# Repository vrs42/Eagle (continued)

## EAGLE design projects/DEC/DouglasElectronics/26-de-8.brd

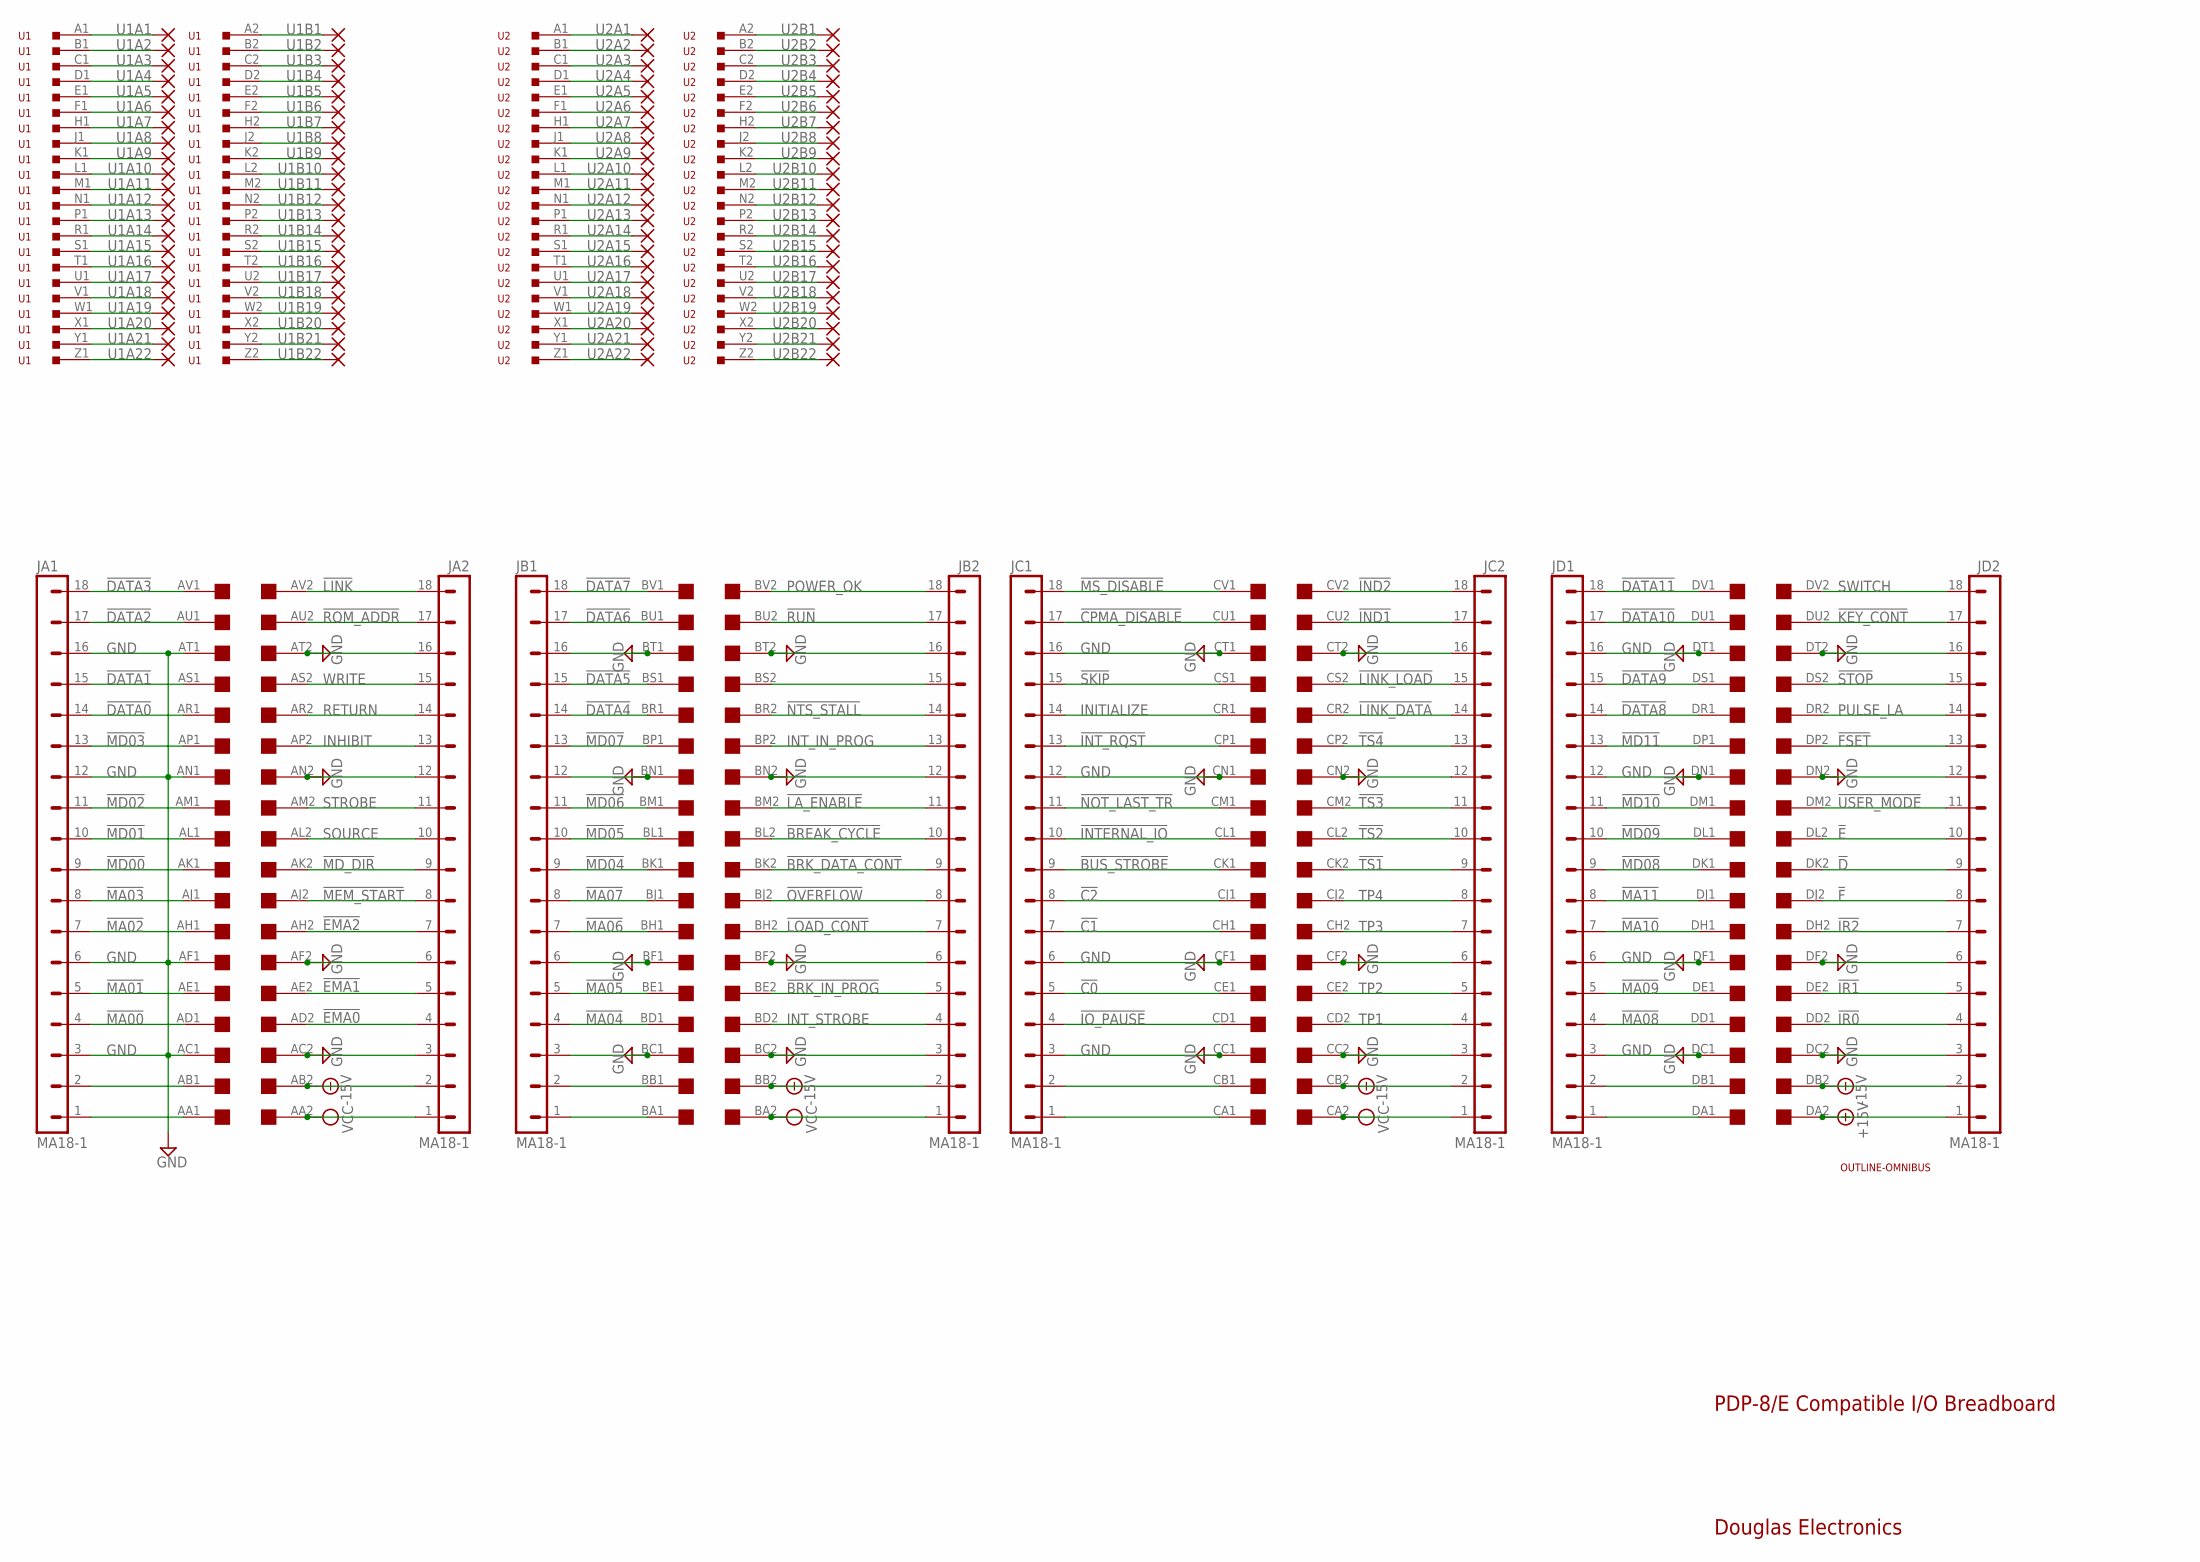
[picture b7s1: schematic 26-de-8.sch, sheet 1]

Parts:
JA1, JA2: MA18-1
JB1, JB2: MA18-1
JC1, JC2: MA18-1
JD1, JD2: MA18-1
U1, U2: 133-022-03
U1A1, U1A2, U1A3, U1A4, U1A5, U1A6, U1A7, U1A8, U1A9, U1A10, U1A11, U1A12, U1A13, U1A14, U1A15, U1A16, U1A17, U1A18, U1A19, U1A20, U1A21, U1A22, U1B1, U1B2, U1B3, U1B4, U1B5, U1B6, U1B7, U1B8, U1B9, U1B10, U1B11, U1B12, U1B13, U1B14, U1B15, U1B16, U1B17, U1B18, U1B19, U1B20, U1B21, U1B22, U2A1, U2A2, U2A3, U2A4, U2A5, U2A6, U2A7, U2A8, U2A9, U2A10, U2A11, U2A12, U2A13, U2A14, U2A15, U2A16, U2A17, U2A18, U2A19, U2A20, U2A21, U2A22, U2B1, U2B2, U2B3, U2B4, U2B5, U2B6, U2B7, U2B8, U2B9, U2B10, U2B11, U2B12, U2B13, U2B14, U2B15, U2B16, U2B17, U2B18, U2B19, U2B20, U2B21, U2B22: 1,6/0,8
U$1: OUTLINE-OMNIBUS; OMNIBUS
U$2: QUAD; EDGE-CON8

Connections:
!BREAK_CYCLE: JB2.10, U$2.BL2
!BRK_DATA_CONT: JB2.9, U$2.BK2
!BRK_IN_PROG: JB2.5, U$2.BE2
!BUS_STROBE: JC1.9, U$2.CK1
!C0: JC1.5, U$2.CE1; also elsewhere on the board
!C1: JC1.7, U$2.CH1; also elsewhere on the board
!C2: JC1.8, U$2.CJ1
!CPMA_DISABLE: JC1.17, U$2.CU1
!D: JD2.9, U$2.DK2
!DATA0: JA1.14, U$2.AR1; also elsewhere on the board
!DATA1: JA1.15, U$2.AS1; also elsewhere on the board
!DATA2: JA1.17, U$2.AU1; also elsewhere on the board
!DATA3: JA1.18, U$2.AV1; also elsewhere on the board
!DATA4: JB1.14, U$2.BR1; also elsewhere on the board
!DATA5: JB1.15, U$2.BS1; also elsewhere on the board
!DATA6: JB1.17, U$2.BU1; also elsewhere on the board
!DATA7: JB1.18, U$2.BV1; also elsewhere on the board
!DATA8: JD1.14, U$2.DR1; also elsewhere on the board
!DATA9: JD1.15, U$2.DS1; also elsewhere on the board
!DATA10: JD1.17, U$2.DU1; also elsewhere on the board
!DATA11: JD1.18, U$2.DV1; also elsewhere on the board
!E: JD2.10, U$2.DL2
!EMA0: JA2.4, U$2.AD2
!EMA1: JA2.5, U$2.AE2
!EMA2: JA2.7, U$2.AH2
!F: JD2.8, U$2.DJ2
!FSET: JD2.13, U$2.DP2
!IND1: JC2.17, U$2.CU2
!IND2: JC2.18, U$2.CV2
!INTERNAL_IO: JC1.10, U$2.CL1; also elsewhere on the board
!INT_RQST: JC1.13, U$2.CP1; also elsewhere on the board
!IO_PAUSE: JC1.4, U$2.CD1; also elsewhere on the board
!IR0: JD2.4, U$2.DD2
!IR1: JD2.5, U$2.DE2
!IR2: JD2.7, U$2.DH2
!KEY_CONT: JD2.17, U$2.DU2
!LA_ENABLE: JB2.11, U$2.BM2
!LINK: JA2.18, U$2.AV2
!LINK_DATA: JC2.14, U$2.CR2
!LINK_LOAD: JC2.15, U$2.CS2
!LOAD_CONT: JB2.7, U$2.BH2
!MA00: JA1.4, U$2.AD1
!MA01: JA1.5, U$2.AE1
!MA02: JA1.7, U$2.AH1
!MA03: JA1.8, U$2.AJ1
!MA04: JB1.4, U$2.BD1
!MA05: JB1.5, U$2.BE1
!MA06: JB1.7, U$2.BH1
!MA07: JB1.8, U$2.BJ1
!MA08: JD1.4, U$2.DD1
!MA09: JD1.5, U$2.DE1
!MA10: JD1.7, U$2.DH1
!MA11: JD1.8, U$2.DJ1
!MD00: JA1.9, U$2.AK1
!MD01: JA1.10, U$2.AL1
!MD02: JA1.11, U$2.AM1
!MD03: JA1.13, U$2.AP1; also elsewhere on the board
!MD04: JB1.9, U$2.BK1; also elsewhere on the board
!MD05: JB1.10, U$2.BL1; also elsewhere on the board
!MD06: JB1.11, U$2.BM1; also elsewhere on the board
!MD07: JB1.13, U$2.BP1; also elsewhere on the board
!MD08: JD1.9, U$2.DK1; also elsewhere on the board
!MD09: JD1.10, U$2.DL1; also elsewhere on the board
!MD10: JD1.11, U$2.DM1; also elsewhere on the board
!MD11: JD1.13, U$2.DP1; also elsewhere on the board
!MD_DIR: JA2.9, U$2.AK2
!MEM_START: JA2.8, U$2.AJ2
!MS_DISABLE: JC1.18, U$2.CV1
!NOT_LAST_TR: JC1.11, U$2.CM1
!NTS_STALL: JB2.14, U$2.BR2
!OVERFLOW: JB2.8, U$2.BJ2
!ROM_ADDR: JA2.17, U$2.AU2
!RUN: JB2.17, U$2.BU2
!SKIP: JC1.15, U$2.CS1; also elsewhere on the board
!STOP: JD2.15, U$2.DS2
!TS1: JC2.9, U$2.CK2
!TS2: JC2.10, U$2.CL2
!TS3: JC2.11, U$2.CM2
!TS4: JC2.13, U$2.CP2
!USER_MODE: JD2.11, U$2.DM2
+15V: JD2.1, U$2.DA2
-15V: JA2.2, JB2.2, JC2.2, JD2.2, U$2.AB2, U$2.BB2, U$2.CB2, U$2.DB2
GND: JA1.3, JA1.6, JA1.12, JA1.16, JA2.3, JA2.6, JA2.12, JA2.16, JB1.3, JB1.6, JB1.12, JB1.16, JB2.3, JB2.6, JB2.12, JB2.16, JC1.3, JC1.6, JC1.12, JC1.16, JC2.3, JC2.6, JC2.12, JC2.16, JD1.3, JD1.6, JD1.12, JD1.16, JD2.3, JD2.6, JD2.12, JD2.16, U$2.AC1, U$2.AC2, U$2.AF1, U$2.AF2, U$2.AN1, U$2.AN2, U$2.AT1, U$2.AT2, U$2.BC1, U$2.BC2, U$2.BF1, U$2.BF2, U$2.BN1, U$2.BN2, U$2.BT1, U$2.BT2, U$2.CC1, U$2.CC2, U$2.CF1, U$2.CF2, U$2.CN1, U$2.CN2, U$2.CT1, U$2.CT2, U$2.DC1, U$2.DC2, U$2.DF1, U$2.DF2, U$2.DN1, U$2.DN2, U$2.DT1, U$2.DT2; also elsewhere on the board
INHIBIT: JA2.13, U$2.AP2
INITIALIZE: JC1.14, U$2.CR1
INT_IN_PROG: JB2.13, U$2.BP2
INT_STROBE: JB2.4, U$2.BD2
unnamed: JA1.2, U$2.AB1
unnamed: JA1.1, U$2.AA1
unnamed: JB1.2, U$2.BB1
unnamed: JB1.1, U$2.BA1
unnamed: JC1.1, U$2.CA1
unnamed: JB2.15, U$2.BS2
unnamed: JC1.2, U$2.CB1
unnamed: JD1.1, U$2.DA1
unnamed: JD1.2, U$2.DB1
unnamed: U1.A2, U1B1.1
unnamed: U1.B1, U1A2.1
unnamed: U1.C1, U1A3.1
unnamed: U1.D1, U1A4.1
unnamed: U1.E1, U1A5.1
unnamed: U1.F1, U1A6.1
unnamed: U1.H1, U1A7.1
unnamed: U1.J1, U1A8.1
unnamed: U1.K1, U1A9.1
unnamed: U1.L1, U1A10.1
unnamed: U1.M1, U1A11.1
unnamed: U1.N1, U1A12.1
unnamed: U1.P1, U1A13.1
unnamed: U1.R1, U1A14.1
unnamed: U1.S1, U1A15.1
unnamed: U1.T1, U1A16.1
unnamed: U1.U1, U1A17.1
unnamed: U1.V1, U1A18.1
unnamed: U1.W1, U1A19.1
unnamed: U1.X1, U1A20.1
unnamed: U1.Y1, U1A21.1
unnamed: U1.Z1, U1A22.1
unnamed: U1.A1, U1A1.1
unnamed: U1.B2, U1B2.1
unnamed: U1.C2, U1B3.1
unnamed: U1.D2, U1B4.1
unnamed: U1.E2, U1B5.1
unnamed: U1.F2, U1B6.1
unnamed: U1.H2, U1B7.1
unnamed: U1.J2, U1B8.1
unnamed: U1.K2, U1B9.1
unnamed: U1.L2, U1B10.1
unnamed: U1.M2, U1B11.1
unnamed: U1.N2, U1B12.1
unnamed: U1.P2, U1B13.1
unnamed: U1.R2, U1B14.1
unnamed: U1.S2, U1B15.1
unnamed: U1.T2, U1B16.1
unnamed: U1.U2, U1B17.1
unnamed: U1.V2, U1B18.1
unnamed: U1.W2, U1B19.1
unnamed: U1.X2, U1B20.1
unnamed: U1.Y2, U1B21.1
unnamed: U1.Z2, U1B22.1
unnamed: U2.A1, U2A1.1
unnamed: U2.A2, U2B1.1
unnamed: U2.B1, U2A2.1
unnamed: U2.C1, U2A3.1
unnamed: U2.D1, U2A4.1
unnamed: U2.E1, U2A5.1
unnamed: U2.F1, U2A6.1
unnamed: U2.H1, U2A7.1
unnamed: U2.J1, U2A8.1
unnamed: U2.K1, U2A9.1
unnamed: U2.L1, U2A10.1
unnamed: U2.M1, U2A11.1
unnamed: U2.N1, U2A12.1
unnamed: U2.P1, U2A13.1
unnamed: U2.R1, U2A14.1
unnamed: U2.S1, U2A15.1
unnamed: U2.T1, U2A16.1
unnamed: U2.U1, U2A17.1
unnamed: U2.V1, U2A18.1
unnamed: U2.W1, U2A19.1
unnamed: U2.X1, U2A20.1
unnamed: U2.Y1, U2A21.1
unnamed: U2.Z1, U2A22.1
unnamed: U2.B2, U2B2.1
unnamed: U2.C2, U2B3.1
unnamed: U2.D2, U2B4.1
unnamed: U2.E2, U2B5.1
unnamed: U2.F2, U2B6.1
unnamed: U2.H2, U2B7.1
unnamed: U2.J2, U2B8.1
unnamed: U2.K2, U2B9.1
unnamed: U2.L2, U2B10.1
unnamed: U2.M2, U2B11.1
unnamed: U2.N2, U2B12.1
unnamed: U2.P2, U2B13.1
unnamed: U2.R2, U2B14.1
unnamed: U2.S2, U2B15.1
unnamed: U2.T2, U2B16.1
unnamed: U2.U2, U2B17.1
unnamed: U2.V2, U2B18.1
unnamed: U2.W2, U2B19.1
unnamed: U2.X2, U2B20.1
unnamed: U2.Y2, U2B21.1
unnamed: U2.Z2, U2B22.1
POWER_OK: JB2.18, U$2.BV2
PULSE_LA: JD2.14, U$2.DR2
RETURN: JA2.14, U$2.AR2
SOURCE: JA2.10, U$2.AL2
STROBE: JA2.11, U$2.AM2
SWITCH: JD2.18, U$2.DV2
TP1: JC2.4, U$2.CD2
TP2: JC2.5, U$2.CE2
TP3: JC2.7, U$2.CH2; also elsewhere on the board
TP4: JC2.8, U$2.CJ2
VCC: JA2.1, JB2.1, JC2.1, U$2.AA2, U$2.BA2, U$2.CA2; also elsewhere on the board
WRITE: JA2.15, U$2.AS2

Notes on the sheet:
PDP-8/E Compatible I/O Breadboard
Douglas Electronics

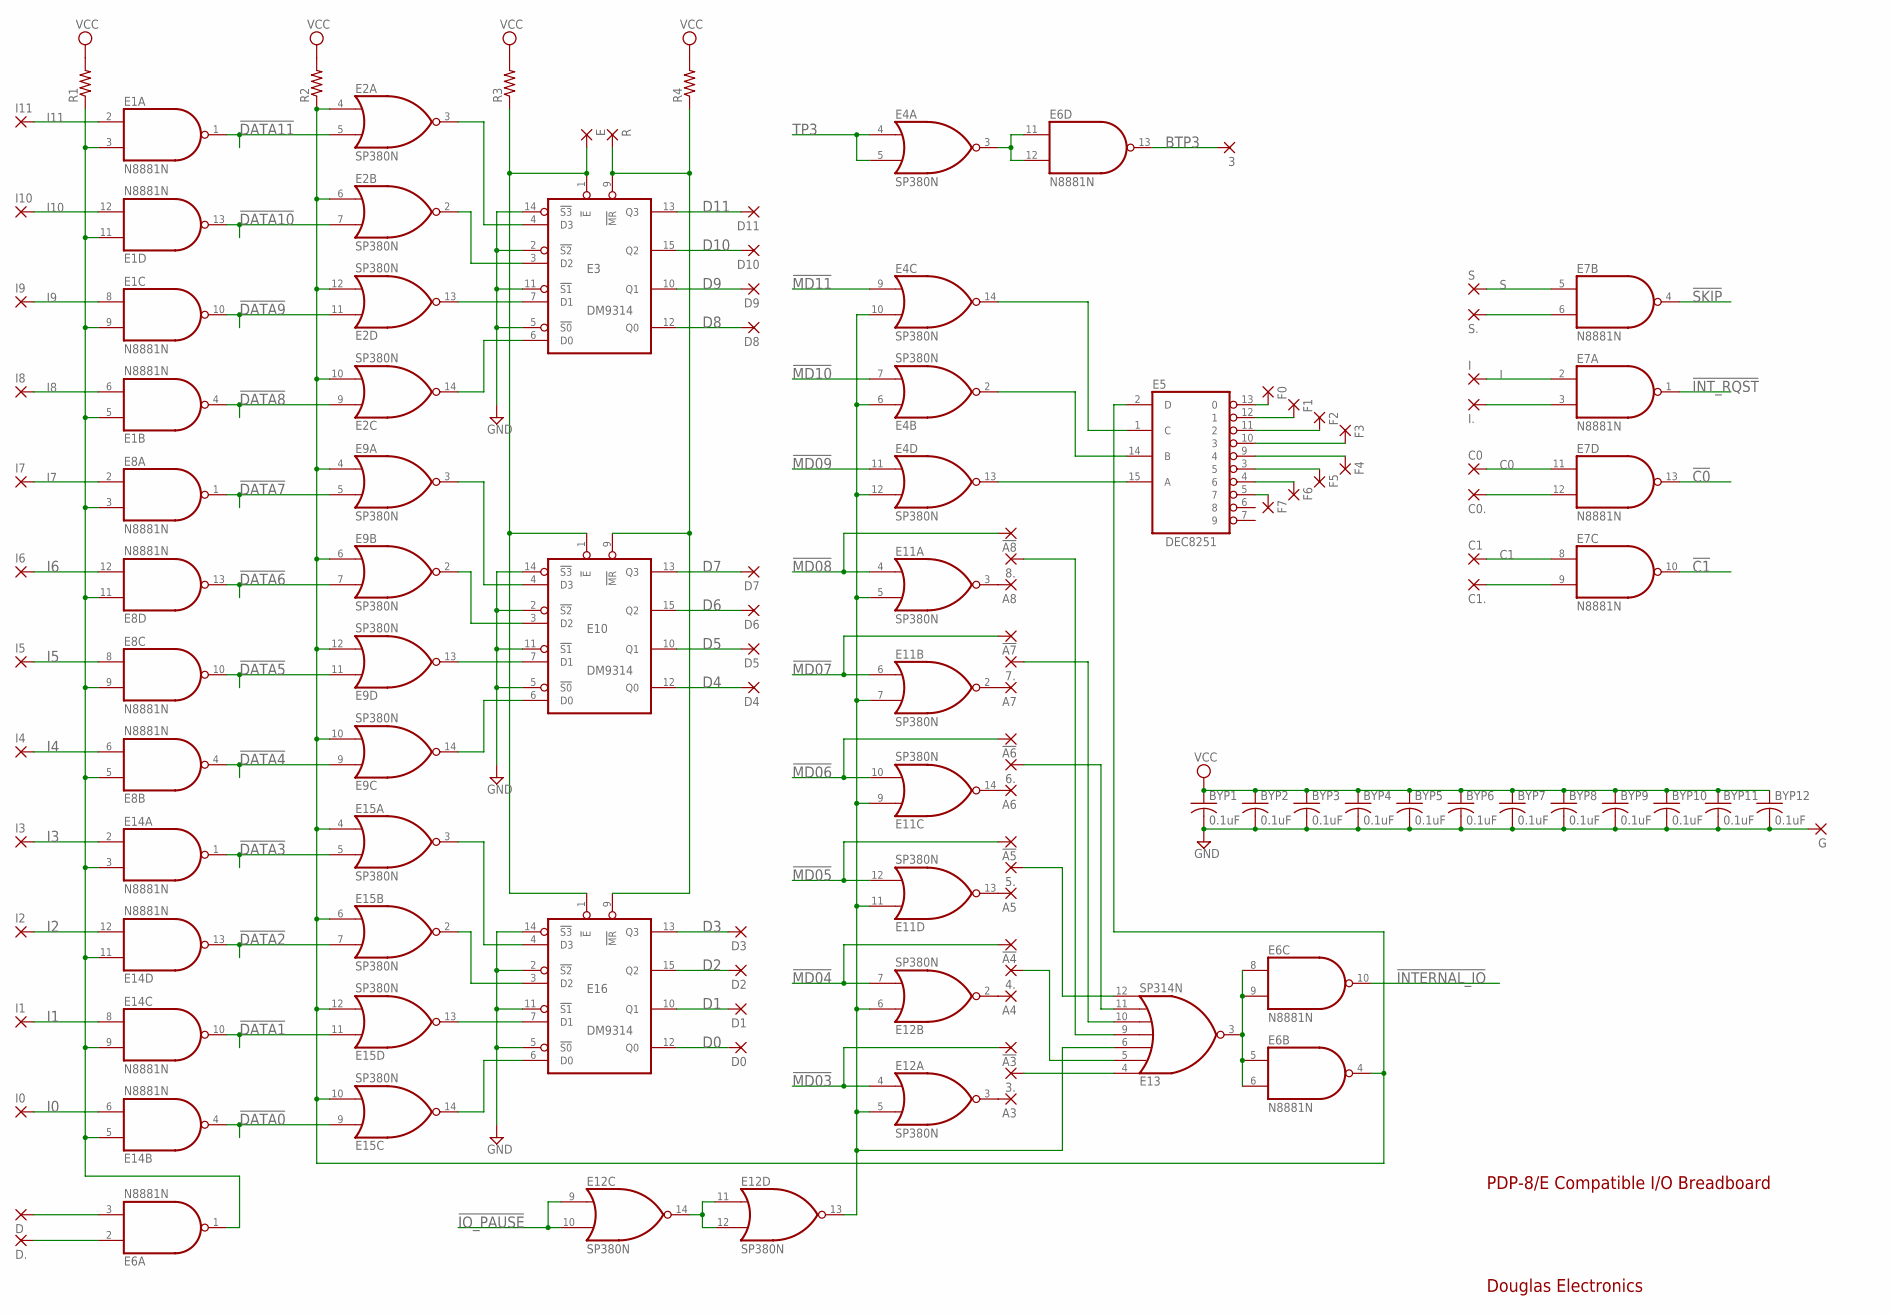
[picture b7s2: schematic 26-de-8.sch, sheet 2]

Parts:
3, 3., 4., 5., 6., 7., 8.: 1,6/0,8
!A3, !A4, !A5, !A6, !A7, !A8: 1,6/0,8
A3, A4, A5, A6, A7, A8: 1,6/0,8
BYP1, BYP2, BYP3, BYP4, BYP5, BYP6, BYP7, BYP8, BYP9, BYP10, BYP11, BYP12: 0.1uF; C050-025X075
C0, C0., C1, C1.: 1,6/0,8
D, D0, D1, D2, D3, D4, D5, D6, D7, D8, D9, D10, D11, D.: 1,6/0,8
E: 1,6/0,8
E1, E6, E7, E8, E14: N8881N; DIL14
E2, E4, E9, E11, E12, E15: SP380N; DIL14
E3, E10, E16: DM9314; DIL16
E5: DEC8251; DIL16
E13: SP314N; DIL14
F0, F1, F2, F3, F4, F5, F6, F7: 1,6/0,8
G: 1,6/0,8
I, I0, I1, I2, I3, I4, I5, I6, I7, I8, I9, I10, I11, I.: 1,6/0,8
R: 1,6/0,8
R1, R2, R3, R4: R-US_0207/10; 0207/10
S, S.: 1,6/0,8

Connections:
!C0: E7.13 (O); also elsewhere on the board
!C1: E7.10 (O); also elsewhere on the board
!DATA0: E14.4 (O), E15.9 (I0); also elsewhere on the board
!DATA1: E14.10 (O), E15.11 (I0); also elsewhere on the board
!DATA2: E14.13 (O), E15.7 (I1); also elsewhere on the board
!DATA3: E14.1 (O), E15.5 (I1); also elsewhere on the board
!DATA4: E8.4 (O), E9.9 (I0); also elsewhere on the board
!DATA5: E8.10 (O), E9.11 (I0); also elsewhere on the board
!DATA6: E8.13 (O), E9.7 (I1); also elsewhere on the board
!DATA7: E8.1 (O), E9.5 (I1); also elsewhere on the board
!DATA8: E1.4 (O), E2.9 (I0); also elsewhere on the board
!DATA9: E1.10 (O), E2.11 (I0); also elsewhere on the board
!DATA10: E1.13 (O), E2.7 (I1); also elsewhere on the board
!DATA11: E1.1 (O), E2.5 (I1); also elsewhere on the board
!INTERNAL_IO: E6.10 (O); also elsewhere on the board
!INT_RQST: E7.1 (O); also elsewhere on the board
!IO_PAUSE: E12.9 (I0), E12.10 (I1); also elsewhere on the board
!MD03: !A3.1, E12.4 (I0); also elsewhere on the board
!MD04: !A4.1, E12.7 (I1); also elsewhere on the board
!MD05: !A5.1, E11.12 (I1); also elsewhere on the board
!MD06: !A6.1, E11.10 (I1); also elsewhere on the board
!MD07: !A7.1, E11.6 (I0); also elsewhere on the board
!MD08: !A8.1, E11.4 (I0); also elsewhere on the board
!MD09: E4.11 (I0); also elsewhere on the board
!MD10: E4.7 (I1); also elsewhere on the board
!MD11: E4.9 (I0); also elsewhere on the board
!SKIP: E7.4 (O); also elsewhere on the board
BTP3: 3.1, E6.13 (O)
C0: C0.1, E7.11 (I0)
C1: C1.1, E7.8 (I0)
D0: D0.1, E16.12 (Q0)
D1: D1.1, E16.10 (Q1)
D2: D2.1, E16.15 (Q2)
D3: D3.1, E16.13 (Q3)
D4: D4.1, E10.12 (Q0)
D5: D5.1, E10.10 (Q1)
D6: D6.1, E10.15 (Q2)
D7: D7.1, E10.13 (Q3)
D8: D8.1, E3.12 (Q0)
D9: D9.1, E3.10 (Q1)
D10: D10.1, E3.15 (Q2)
D11: D11.1, E3.13 (Q3)
GND: BYP1.2, BYP2.2, BYP3.2, BYP4.2, BYP5.2, BYP6.2, BYP7.2, BYP8.2, BYP9.2, BYP10.2, BYP11.2, BYP12.2, E1.7 (GND), E2.1 (GND), E3.2 (!S2), E3.5 (!S0), E3.8 (GND), E3.11 (!S1), E3.14 (!S3), E4.1 (GND), E5.8 (GND), E6.7 (GND), E7.7 (GND), E8.7 (GND), E9.1 (GND), E10.2 (!S2), E10.5 (!S0), E10.8 (GND), E10.11 (!S1), E10.14 (!S3), E11.1 (GND), E12.1 (GND), E13.1 (GND), E14.7 (GND), E15.1 (GND), E16.2 (!S2), E16.5 (!S0), E16.8 (GND), E16.11 (!S1), E16.14 (!S3), G.1; also elsewhere on the board
I: E7.2 (I0), I.1
I0: E14.6 (I1), I0.1
I1: E14.8 (I0), I1.1
I2: E14.12 (I1), I2.1
I3: E14.2 (I0), I3.1
I4: E8.6 (I1), I4.1
I5: E8.8 (I0), I5.1
I6: E8.12 (I1), I6.1
I7: E8.2 (I0), I7.1
I8: E1.6 (I1), I8.1
I9: E1.8 (I0), I9.1
I10: E1.12 (I1), I10.1
I11: E1.2 (I0), I11.1
unnamed: E1.3 (I1), E1.5 (I0), E1.9 (I1), E1.11 (I0), E6.1 (O), E8.3 (I1), E8.5 (I0), E8.9 (I1), E8.11 (I0), E14.3 (I1), E14.5 (I0), E14.9 (I1), E14.11 (I0), R1.1
unnamed: E5.13 (0), F0.1
unnamed: E5.12 (1), F1.1
unnamed: E5.11 (2), F2.1
unnamed: E5.10 (3), F3.1
unnamed: E5.9 (4), F4.1
unnamed: E5.3 (5), F5.1
unnamed: E5.4 (6), F6.1
unnamed: E5.5 (7), F7.1
unnamed: E2.4 (I0), E2.6 (I0), E2.10 (I1), E2.12 (I1), E5.2 (D), E6.4 (O), E9.4 (I0), E9.6 (I0), E9.10 (I1), E9.12 (I1), E15.4 (I0), E15.6 (I0), E15.10 (I1), E15.12 (I1), R2.1
unnamed: E15.14 (O), E16.6 (D0)
unnamed: E15.3 (O), E16.4 (D3)
unnamed: E9.13 (O), E10.7 (D1)
unnamed: E9.14 (O), E10.6 (D0)
unnamed: E15.13 (O), E16.7 (D1)
unnamed: E9.2 (O), E10.3 (D2)
unnamed: E15.2 (O), E16.3 (D2)
unnamed: E9.3 (O), E10.4 (D3)
unnamed: E2.3 (O), E3.4 (D3)
unnamed: E2.2 (O), E3.3 (D2)
unnamed: E2.13 (O), E3.7 (D1)
unnamed: E2.14 (O), E3.6 (D0)
unnamed: E.1, E3.1 (!E), E10.1 (!E), E16.1 (!E), R3.1
unnamed: E3.9 (!MR), E10.9 (!MR), E16.9 (!MR), R.1, R4.1
unnamed: E4.6 (I0), E4.10 (I1), E4.12 (I1), E11.5 (I1), E11.7 (I1), E11.9 (I0), E11.11 (I0), E12.5 (I1), E12.6 (I0), E12.13 (O), E13.6 (I2)
unnamed: E4.14 (O), E5.1 (C)
unnamed: E12.11 (I0), E12.12 (I1), E12.14 (O)
unnamed: E6.5 (I0), E6.6 (I1), E6.8 (I0), E6.9 (I1), E13.3 (O)
unnamed: A3.1, E12.3 (O)
unnamed: A6.1, E11.14 (O)
unnamed: A7.1, E11.2 (O)
unnamed: A4.1, E12.2 (O)
unnamed: E4.2 (O), E5.14 (B)
unnamed: 3..1, E13.4 (I0)
unnamed: 4..1, E13.5 (I1)
unnamed: A5.1, E11.13 (O)
unnamed: 5..1, E13.12 (I6)
unnamed: E4.13 (O), E5.15 (A)
unnamed: E4.3 (O), E6.11 (I0), E6.12 (I1)
unnamed: D..1, E6.2 (I0)
unnamed: D.1, E6.3 (I1)
unnamed: A8.1, E11.3 (O)
unnamed: 8..1, E13.9 (I3)
unnamed: 7..1, E13.10 (I4)
unnamed: 6..1, E13.11 (I5)
unnamed: E7.6 (I1), S..1
unnamed: E7.3 (I1), I..1
unnamed: C0..1, E7.12 (I1)
unnamed: C1..1, E7.9 (I1)
S: E7.5 (I0), S.1
TP3: E4.4 (I0), E4.5 (I1); also elsewhere on the board
VCC: BYP1.1, BYP2.1, BYP3.1, BYP4.1, BYP5.1, BYP6.1, BYP7.1, BYP8.1, BYP9.1, BYP10.1, BYP11.1, BYP12.1, E1.14 (VCC), E2.8 (VCC), E3.16 (VCC), E4.8 (VCC), E5.16 (VCC), E6.14 (VCC), E7.14 (VCC), E8.14 (VCC), E9.8 (VCC), E10.16 (VCC), E11.8 (VCC), E12.8 (VCC), E13.8 (VCC), E14.14 (VCC), E15.8 (VCC), E16.16 (VCC), R1.2, R2.2, R3.2, R4.2; also elsewhere on the board

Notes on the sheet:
PDP-8/E Compatible I/O Breadboard
Douglas Electronics
